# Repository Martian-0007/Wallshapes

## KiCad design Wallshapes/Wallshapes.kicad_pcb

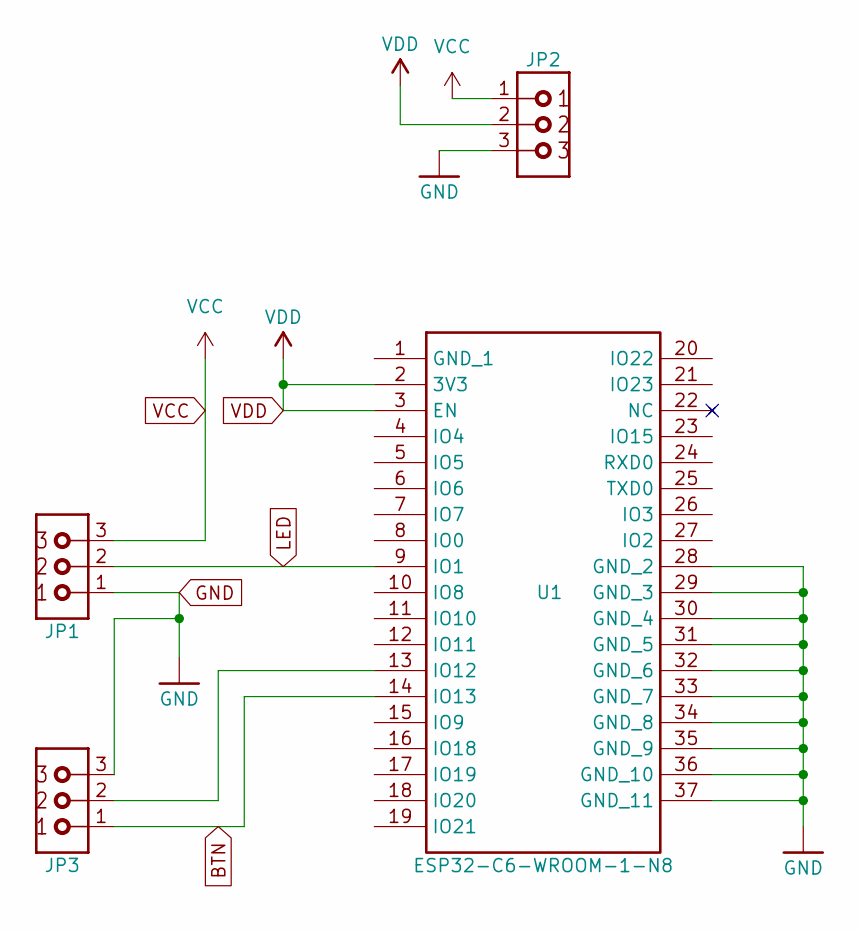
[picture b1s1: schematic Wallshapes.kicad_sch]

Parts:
JP1, JP2, JP3: BC-HEADER-3-PIN-THT; Manufacturer Part Number 61300311121
U1: ESP32-C6-WROOM-1-N8; ESP32-C6-WROOM-1-N8_R; Mouser Part Number 356-ESP32C6WROOM1N8

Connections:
BTN: JP3.1, U1.14 (IO13)
GND: JP1.1, JP2.3, JP3.3, U1.28 (GND_2), U1.29 (GND_3), U1.30 (GND_4), U1.31 (GND_5), U1.32 (GND_6), U1.33 (GND_7), U1.34 (GND_8), U1.35 (GND_9), U1.36 (GND_10), U1.37 (GND_11)
LED: JP1.2, U1.9 (IO1)
unnamed: JP3.2, U1.13 (IO12)
VCC: JP1.3, JP2.1
VDD: JP2.2, U1.2 (3V3), U1.3 (EN)

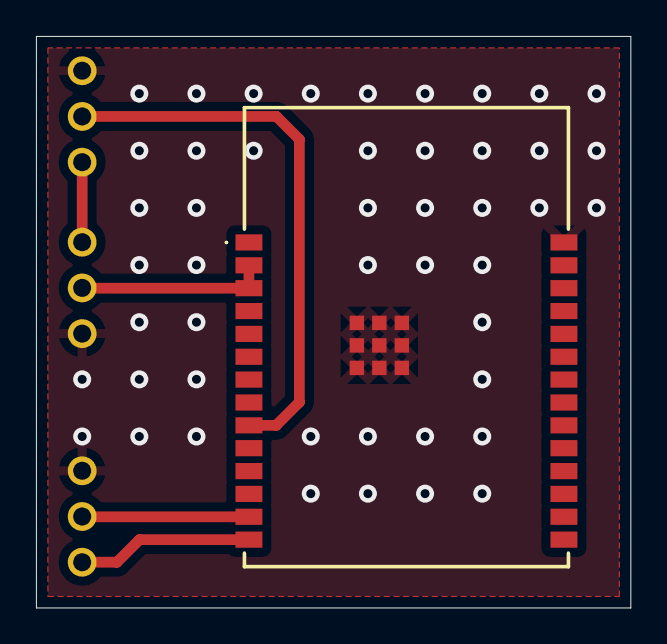
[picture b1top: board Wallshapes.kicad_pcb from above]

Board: 4 copper layers, 33.0 x 31.8 mm, 4 parts (0 on the bottom side), 6 nets.

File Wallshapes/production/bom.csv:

Designator,Footprint,Quantity,Value,LCSC Part #
JP1,BC-HEADER-3-PIN-SOCKET-THT,1,~,
JP2,BC-HEADER-3-PIN-THT,1,~,
U1,ESP32-C6-WROOM-1-N8_R,1,ESP32-C6-WROOM-1-N8,

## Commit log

2024-11-21 brightness regulation
2024-11-22 Add PCB
2024-11-23 Color wheel + photo brightness NodeMCU v1
2024-11-24 3 Nodes with sync
2024-11-24 Add ESPHome integration
2024-11-24 Edit brightness value
2024-11-25 Add switch to esphome
2024-12-02 Switch to 7 more nodes
